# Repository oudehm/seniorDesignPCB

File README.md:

# Senior Design PCBs

Editable KiCad projects for the brain, light, power, and pump boards.

## Board previews

3D renders from the KiCad designs. Parts without available 3D models may not appear.

### Brain board

The main STM32 controller connects the environmental sensors and display, and provides control signals for the lights, dosing pumps, fans, and cooler.

### Light board

Four MOSFET channels switch the blue, red, near-infrared, and white grow lights using PWM signals from the brain board.

### Power board

Distributes the 12 V supply through fused branches and generates 5 V and 3.3 V rails for the system. It also includes the cooler switching circuit.

### Pump board

Five MOSFET driver channels control the Micro, Grow, Bloom, pH-up, and pH-down dosing pumps, with flyback diodes for the pump loads.

## Open the designs

1. Install KiCad 10.0.3 or newer with the standard symbol, footprint, and 3D model libraries.
2. Clone this repository or download and extract the entire ZIP, keeping the folder structure intact.
3. In KiCad, open the project you want:
   - `brain_PCB/brain_PCB.kicad_pro`
   - `light_PCB/light_PCB.kicad_pro`
   - `power_PCB/power_PCB.kicad_pro`
   - `pump_PCB/pump_PCB.kicad_pro`
4. Open its schematic or PCB from the KiCad project manager.

Custom symbols, footprints, library tables, design rules, and the referenced local USB 3D model are included. Local libraries use `${KIPRJMOD}` paths so they work wherever you extract the repository. The USB model is a simplified representation.

Manufacturing outputs, review reports, backups, and personal editor settings are excluded. Generate fabrication files from the projects when needed.

Some power-board 3D models (the 6-pin and 10-pin Molex Micro-Fit connectors and Littelfuse NANO2 fuse) were unavailable in the KiCad 10.0.3 libraries used for verification. Their schematic symbols and PCB footprints are included in the designs; these parts may be absent from the 3D view.

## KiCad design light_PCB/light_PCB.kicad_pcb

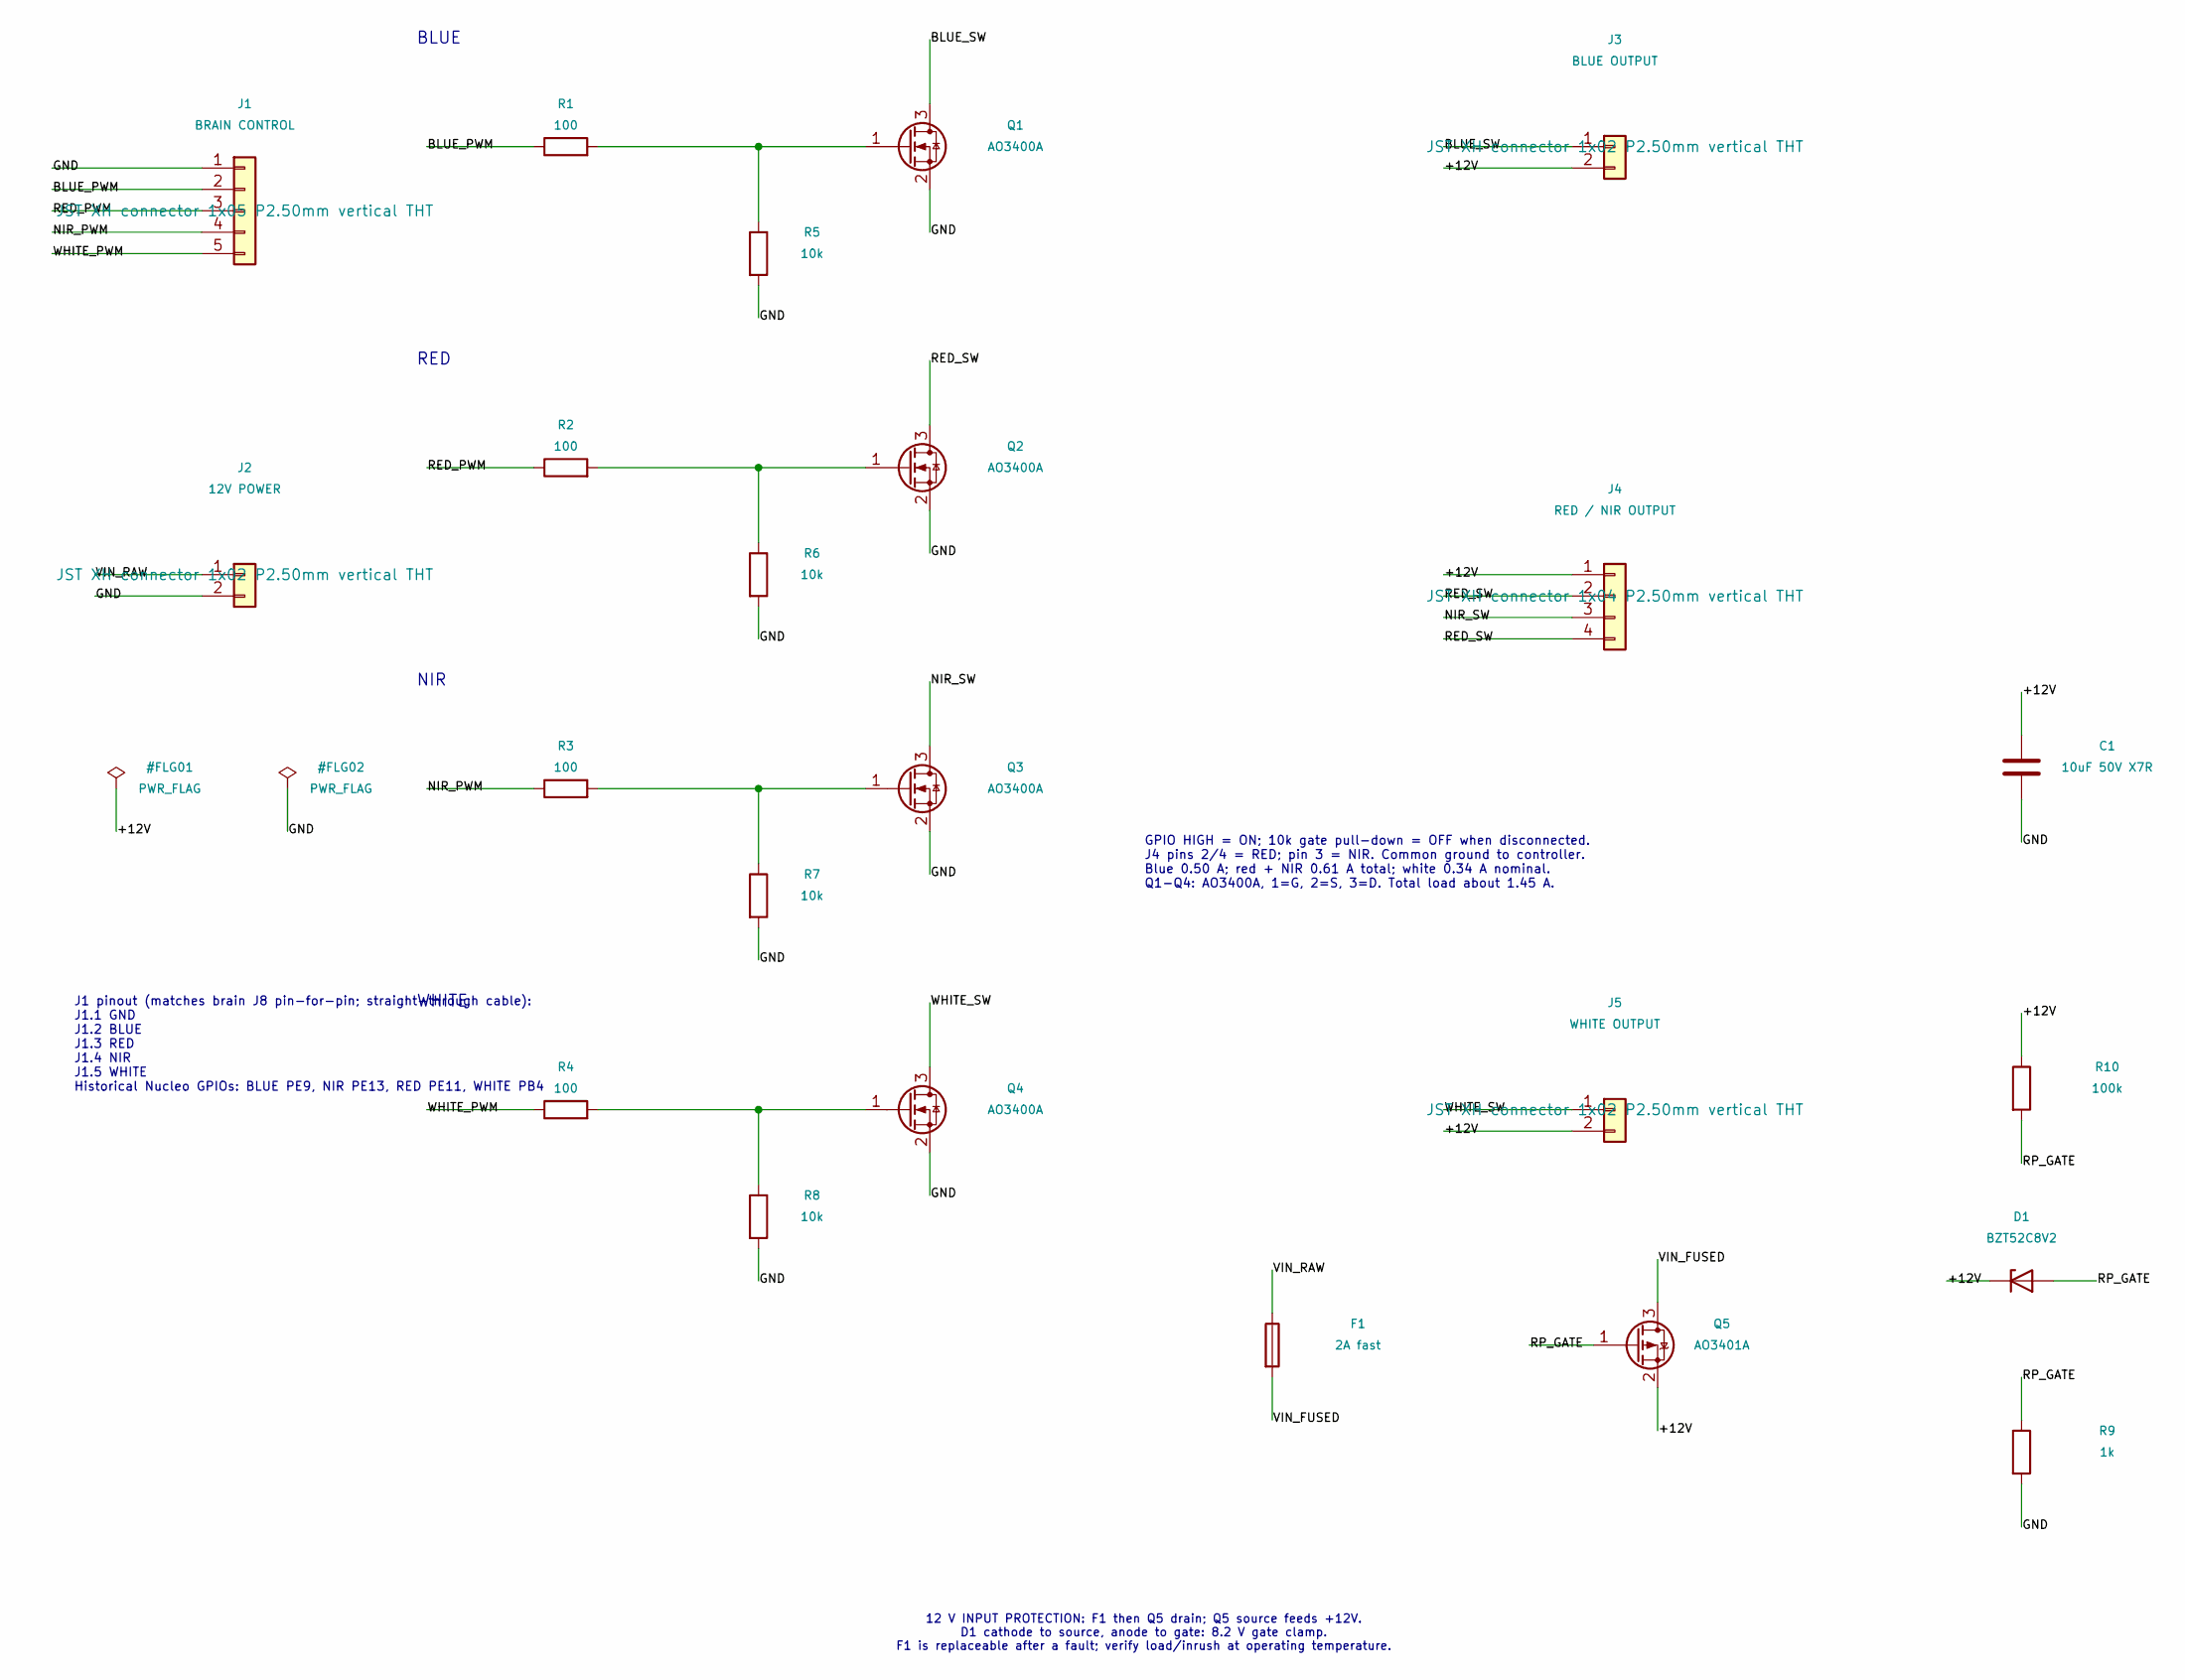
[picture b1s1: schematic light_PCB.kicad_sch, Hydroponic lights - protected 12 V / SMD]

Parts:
C1: 10uF 50V X7R; C_1210_3225Metric; MPN GRM32ER71H106KA12L; LCSC C77102
D1: BZT52C8V2; D_SOD-123; MPN BZT52C8V2-13-F; LCSC C3001623
F1: 2A fast; Fuse_1206_3216Metric; MPN 0466002.NRHF; LCSC C3105
J1: BRAIN CONTROL; JST_XH_B5B-XH-A_1x05_P2.50mm_Vertical; MPN B5B-XH-A(LF)(SN)
J2: 12V POWER; JST_XH_B2B-XH-A_1x02_P2.50mm_Vertical; MPN B2B-XH-A(LF)(SN)
J3: BLUE OUTPUT; JST_XH_B2B-XH-A_1x02_P2.50mm_Vertical; MPN B2B-XH-A(LF)(SN)
J4: RED / NIR OUTPUT; JST_XH_B4B-XH-A_1x04_P2.50mm_Vertical; MPN B4B-XH-A(LF)(SN)
J5: WHITE OUTPUT; JST_XH_B2B-XH-A_1x02_P2.50mm_Vertical; MPN B2B-XH-A(LF)(SN)
Q1, Q2, Q3, Q4: AO3400A; SOT-23; MPN AO3400A; LCSC C20917
Q5: AO3401A; SOT-23; MPN AO3401A; LCSC C15127
R1, R2, R3, R4: 100; R_0402_1005Metric_SilkClearance; MPN RC0402FR-07100RL; LCSC C106232
R5, R6, R7, R8: 10k; R_0402_1005Metric_SilkClearance; MPN RC0402FR-0710KL; LCSC C60490
R9: 1k; R_0603_1608Metric; MPN RC0603FR-071KL; LCSC C22548
R10: 100k; R_0603_1608Metric; MPN RC0603FR-07100KL; LCSC C14675

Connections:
/+12V: C1.1, D1.1 (K), J3.2, J4.1, J5.2, Q5.2 (S), R10.1
/BLUE_PWM: J1.2, R1.1
/BLUE_SW: J3.1, Q1.3 (D)
/GND: C1.2, J1.1, J2.2, Q1.2 (S), Q2.2 (S), Q3.2 (S), Q4.2 (S), R5.2, R6.2, R7.2, R8.2, R9.2
/NIR_PWM: J1.4, R3.1
/NIR_SW: J4.3, Q3.3 (D)
/RED_PWM: J1.3, R2.1
/RED_SW: J4.2, J4.4, Q2.3 (D)
/RP_GATE: D1.2 (A), Q5.1 (G), R9.1, R10.2
/VIN_FUSED: F1.2, Q5.3 (D)
/VIN_RAW: F1.1, J2.1
/WHITE_PWM: J1.5, R4.1
/WHITE_SW: J5.1, Q4.3 (D)
unnamed: Q1.1 (G), R1.2, R5.1
unnamed: Q2.1 (G), R2.2, R6.1
unnamed: Q3.1 (G), R3.2, R7.1
unnamed: Q4.1 (G), R4.2, R8.1

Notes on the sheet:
12 V INPUT PROTECTION: F1 then Q5 drain; Q5 source feeds +12V. D1 cathode to source, anode to gate: 8.2 V gate clamp. F1 is replaceable after a fault; verify load/inrush at operating temperature.
BLUE
WHITE
J1 pinout (matches brain J8 pin-for-pin; straight-through cable): J1.1 GND J1.2 BLUE J1.3 RED J1.4 NIR J1.5 WHITE Historical Nucleo GPIOs: BLUE PE9, NIR PE13, RED PE11, WHITE PB4
GPIO HIGH = ON; 10k gate pull-down = OFF when disconnected. J4 pins 2/4 = RED; pin 3 = NIR. Common ground to controller. Blue 0.50 A; red + NIR 0.61 A total; white 0.34 A nominal. Q1-Q4: AO3400A, 1=G, 2=S, 3=D. Total load about 1.45 A.
NIR
RED

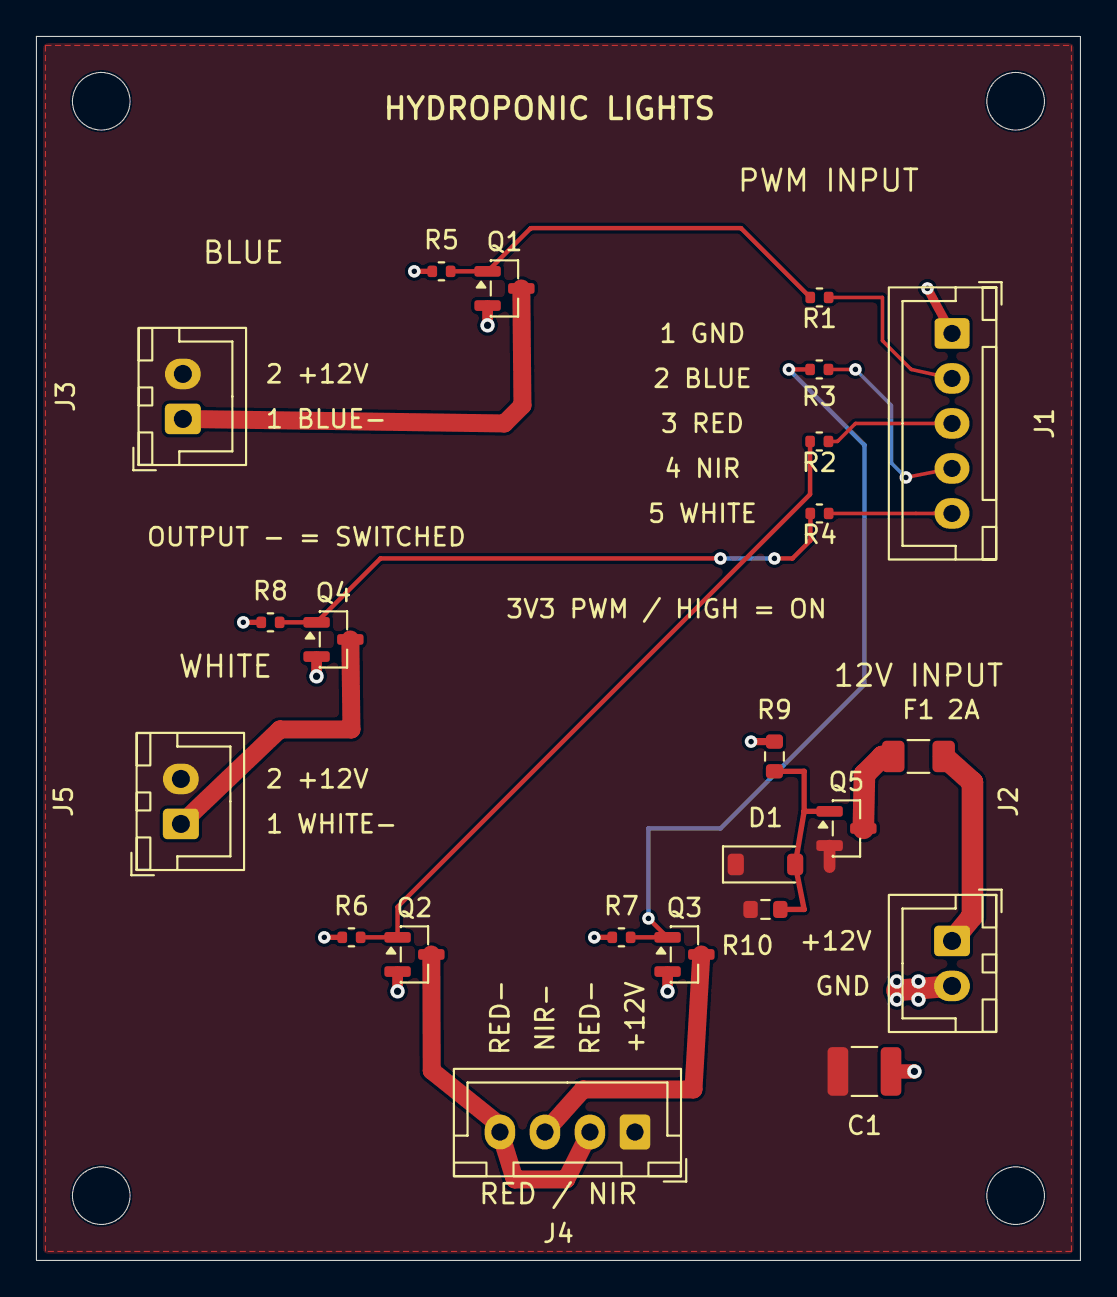
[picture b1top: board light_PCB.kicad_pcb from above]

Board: 2 copper layers, 58.0 x 68.0 mm, 27 parts (0 on the bottom side), 17 nets.

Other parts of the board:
H1, H2, H3, H4: MountingHole_3.2mm_M3
